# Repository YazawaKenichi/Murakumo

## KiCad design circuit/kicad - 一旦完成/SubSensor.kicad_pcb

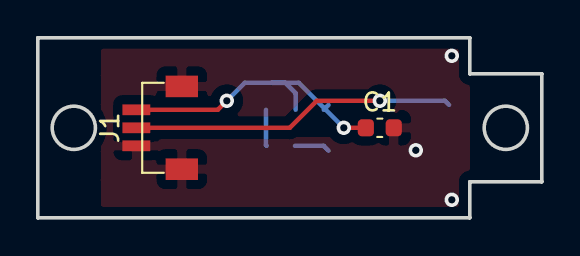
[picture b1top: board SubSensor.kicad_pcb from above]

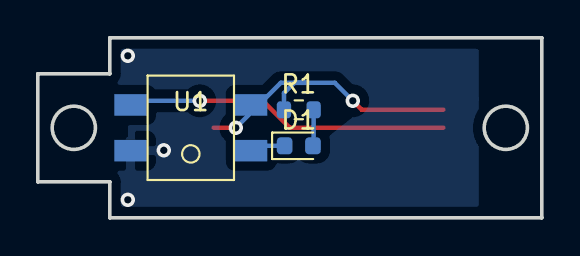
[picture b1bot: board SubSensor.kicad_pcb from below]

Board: 2 copper layers, 28.0 x 10.0 mm, 5 parts (3 on the bottom side), 5 nets.

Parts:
C1: 0.1u; C_0603_1608Metric
D1: SIR19-21C/TR8; D_0603_1608Metric
J1: SH3; SH_01x03
R1: 68; R_0603_1608Metric
U1: S7136

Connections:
+5V: C1.1, J1.3, R1.1, U1.2
GND: C1.2, J1.1, J1.MP, U1.4
unnamed: D1.1, U1.1
unnamed: D1.2, R1.2
unnamed: J1.2, U1.3

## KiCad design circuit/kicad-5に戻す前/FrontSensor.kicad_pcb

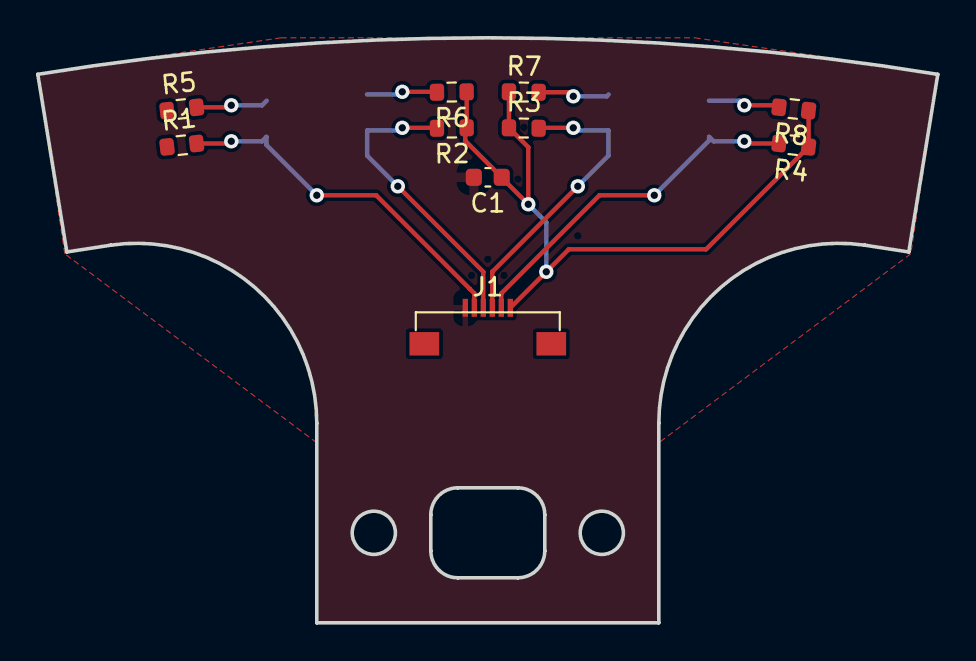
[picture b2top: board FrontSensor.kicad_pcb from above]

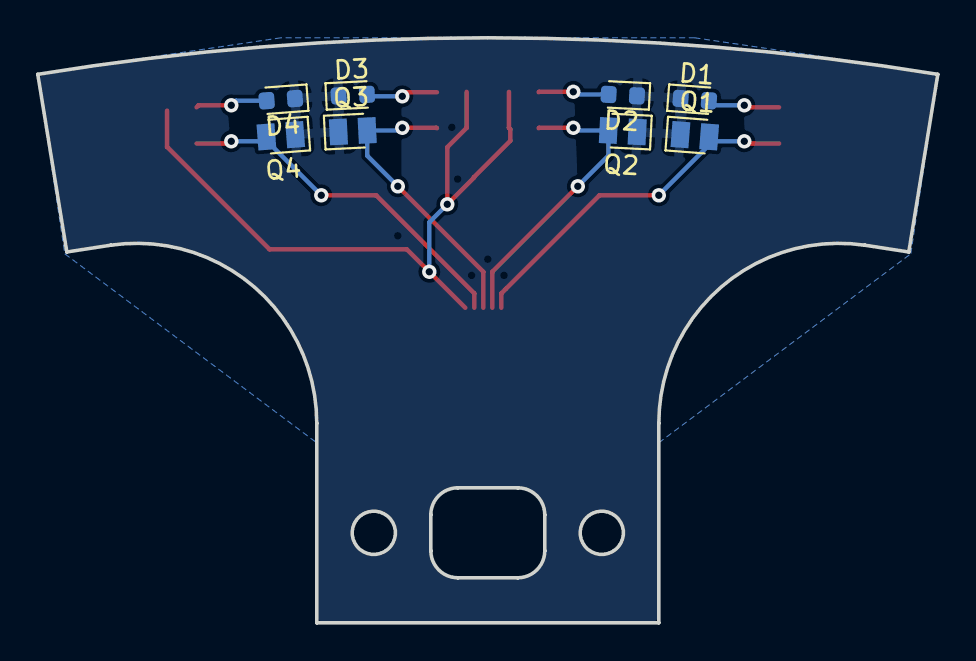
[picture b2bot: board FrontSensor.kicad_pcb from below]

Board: 2 copper layers, 50.0 x 32.5 mm, 18 parts (8 on the bottom side), 10 nets.

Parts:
C1: 0.1u; C_0603_1608Metric
D1, D2, D3, D4: SIR19-21C/TR8; D_0603_1608Metric
J1: FFC6; Molex_0545480671_01x06_P0.5mm
Q1, Q2, Q3, Q4: TEMT7100X01
R1, R2, R3, R4: 10k; R_0603_1608Metric
R5, R6, R7, R8: 100; R_0603_1608Metric

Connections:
+3V3: C1.1, J1.6, R1.1, R2.1, R3.1, R4.1, R5.1, R6.1, R7.1, R8.1
GND: C1.2, D1.1, D2.1, D3.1, D4.1, J1.1, Q1.2, Q2.2, Q3.2, Q4.2
unnamed: D1.2, R5.2
unnamed: D2.2, R6.2
unnamed: D3.2, R7.2
unnamed: D4.2, R8.2
unnamed: J1.2, Q1.1, R1.2
unnamed: J1.3, Q2.1, R2.2
unnamed: J1.4, Q3.1, R3.2
unnamed: J1.5, Q4.1, R4.2

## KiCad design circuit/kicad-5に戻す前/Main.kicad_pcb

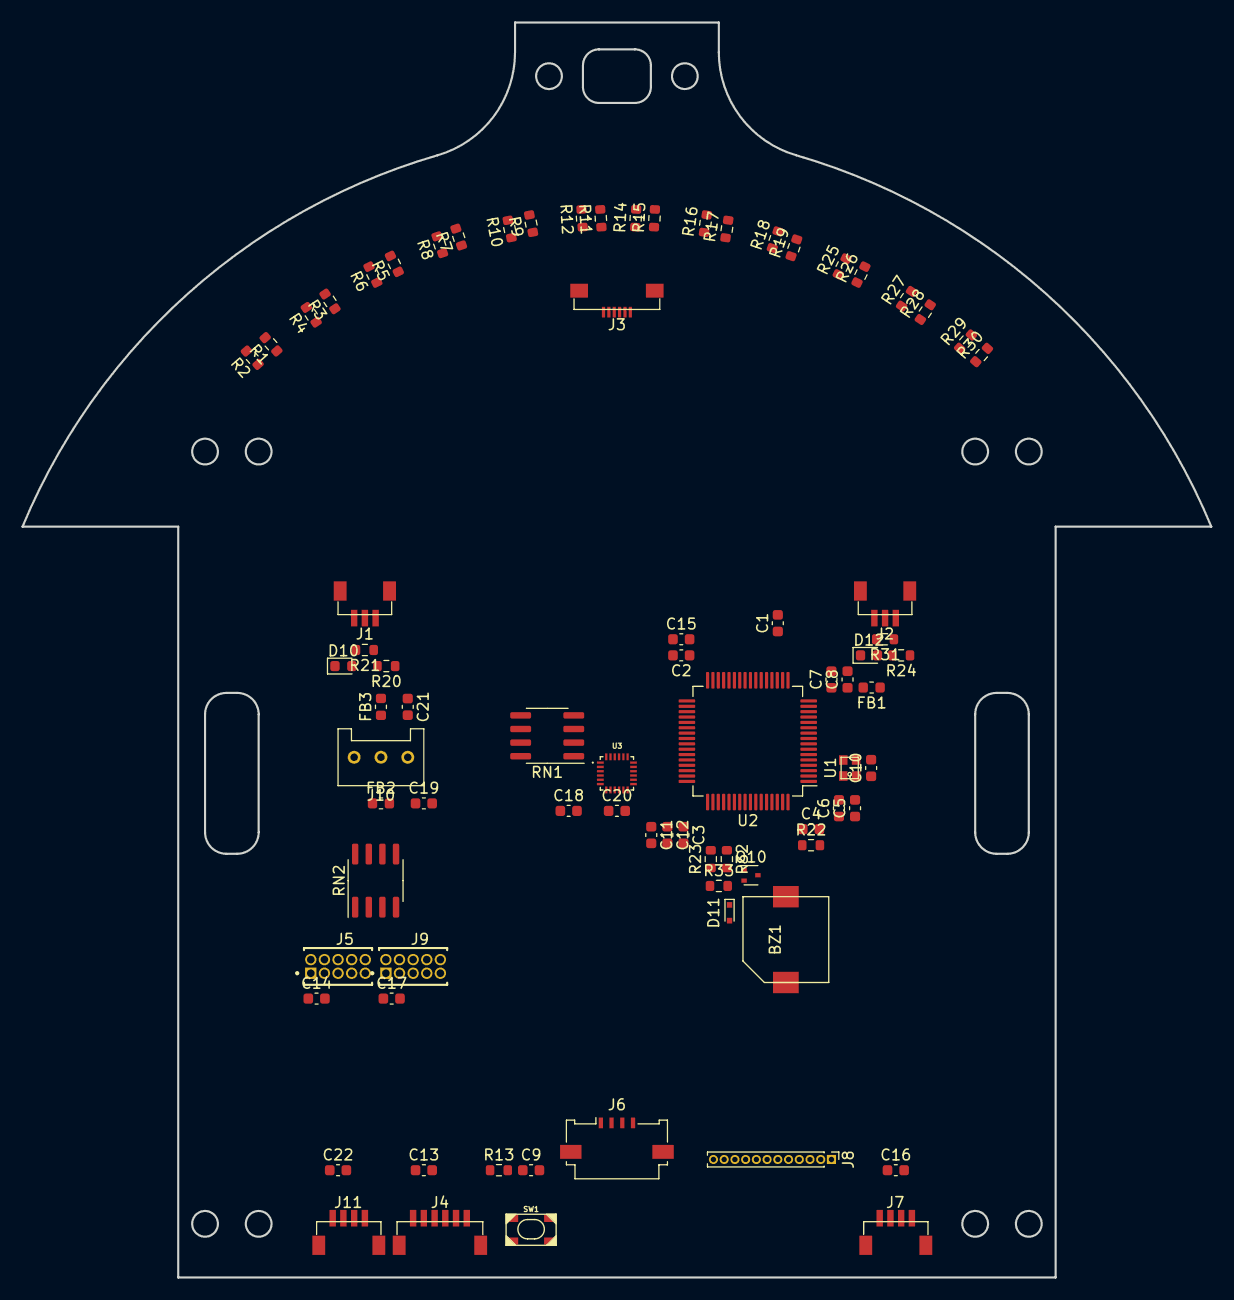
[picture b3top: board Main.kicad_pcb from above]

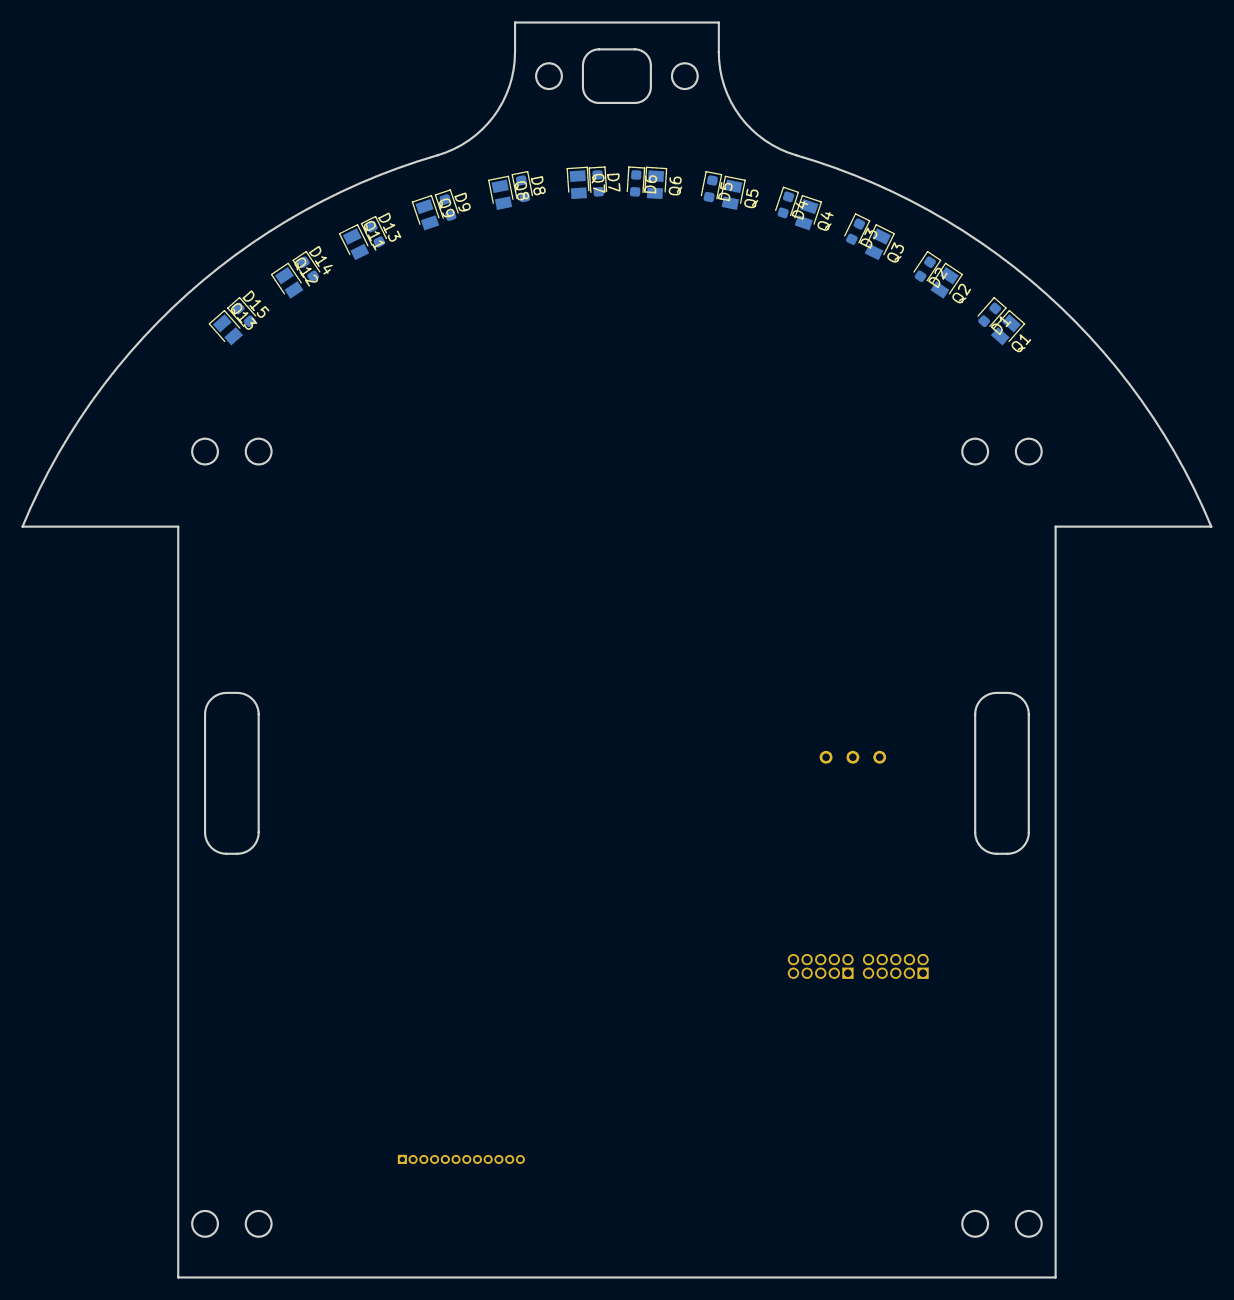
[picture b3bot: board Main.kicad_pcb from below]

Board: 2 copper layers, 110.8 x 117.0 mm, 104 parts (24 on the bottom side), 79 nets, no tracks yet.

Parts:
BZ1: TE044003-4
C1, C2, C3, C4, C6, C7, C9, C10, C13, C14, C15, C16, C17, C18, C19, C20, C21, C22: 0.1u; C_0603_1608Metric
C5: 4.7u; C_0603_1608Metric
C8: 1u; C_0603_1608Metric
C11, C12: 2.2u; C_0603_1608Metric
D1, D2, D3, D4, D5, D6, D7, D8, D9, D13, D14, D15: SIR19-21C/TR8; D_0603_1608Metric
D10, D12: SMLEN3WBC8W1; D_0603_1608Metric
D11: RB751S40-AU_R1_000A1; SOD-523
FB1, FB2, FB3: 470; L_0603_1608Metric
J1, J2: SH3; SH_01x03
J3: FFC6; Molex_0545480671_01x06_P0.5mm
J4: SH6; SH_01x06
J5, J9: FTSH2x5; SAMTEC_FTSH-105-01-L-D-K
J6: FFC4; Molex_200528-0040_1x04-1MP_P1.00mm_Horizontal
J7, J11: SH4; SH_01x04
J8: FFC12; PinHeader_1x12_P1.00mm_Vertical
J10: PA3; PA_01x03
Q1, Q2, Q3, Q4, Q5, Q6, Q7, Q8, Q9, Q11, Q12, Q13: TEMT7100X01
Q10: 2N7002T; SOT-523
R1, R3, R5, R7, R9, R11, R14, R16, R18, R23, R25, R27, R29: 100; R_0603_1608Metric
R2, R4, R6, R8, R10, R12, R13, R15, R17, R19, R21, R22, R26, R28, R30, R31, R32: 10k; R_0603_1608Metric
R20, R24: 470; R_0603_1608Metric
R33: 36; R_0603_1608Metric
RN1, RN2: 10k; SOIC-8_3.9x4.9mm_P1.27mm
SW1: SKRPABE010
U1: ASTMLPA-16MHz-LJ-E-T; ASTMLPA-16.000MHz-LJ-E-T
U2: STM32F405RGTx; LQFP-64_10x10mm_P0.5mm
U3: ICM-20648; QFN40P300X300X95-24N

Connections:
+3V3: BZ1.1, C1.1, C2.1, C3.1, C4.1, C5.1, C6.1, C10.1, C13.1, C15.1, C16.1, C18.1, C21.1, D11.1, FB1.1, FB3.2, J3.1, J4.1, J7.1, R1.1, R2.1, R3.1, R4.1, R5.1, R6.1, R7.1, R8.1, R9.1, R10.1, R11.1, R12.1, R13.1, R14.1, R15.1, R16.1, R17.1, R18.1, R19.1, R25.1, R26.1, R27.1, R28.1, R29.1, R30.1, RN1.5, RN1.6, RN1.7, RN1.8, U1.4, U2.1, U2.19, U2.32, U2.48, U2.64, U3.8, U3.13
+5V: C14.1, C17.1, C19.1, C22.1, FB2.2, J1.1, J2.1, J5.2, J9.2, J11.1, R20.1, R21.1, R24.1, R31.1, RN2.5, RN2.6, RN2.7, RN2.8
/DRV1_EN: J6.1, U2.54
/DRV1_PN: J6.2, U2.58
/DRV2_EN: J6.4, U2.2
/DRV2_PN: J6.3, U2.59
/LED_B: J8.3, U2.51
/LED_G: J8.4, U2.52
/LED_R: J8.5, U2.53
/LED_Red: J8.1, U2.39
/LED_White: J8.2, U2.40
/Rotary1: J8.9, U2.45
/Rotary2: J8.7, U2.44
/Rotary4: J8.6, U2.43
/Rotary8: J8.8, U2.34
/SW1: J8.10, U2.3
/SW2: J8.11, U2.4
/SW3: J8.12, U2.6
/Sensor01: Q1.1, R2.2, U2.27
/Sensor02: Q2.1, R4.2, U2.26
/Sensor03: Q3.1, R6.2, U2.25
/Sensor04: Q4.1, R8.2, U2.24
/Sensor05: Q5.1, R10.2, U2.23
/Sensor06: Q6.1, R12.2, U2.22
/Sensor07: Q7.1, R15.2, U2.21
/Sensor08: Q8.1, R17.2, U2.20
/Sensor09: Q9.1, R19.2, U2.17
/Sensor10: Q11.1, R26.2, U2.16
/Sensor11: Q12.1, R28.2, U2.15
/Sensor12: Q13.1, R30.2, U2.14
Encorder1_A: J5.6, RN2.1, U2.41
Encorder1_B: J5.8, RN2.2, U2.42
Encorder2_A: J9.6, RN2.3, U2.56
Encorder2_B: J9.8, RN2.4, U2.57
GND: C1.2, C2.2, C3.2, C4.2, C5.2, C6.2, C7.2, C8.2, C9.2, C10.2, C11.2, C12.2, C13.2, C14.2, C15.2, C16.2, C17.2, C18.2, C19.2, C20.2, C21.2, C22.2, D1.1, D2.1, D3.1, D4.1, D5.1, D6.1, D7.1, D8.1, D9.1, D13.1, D14.1, D15.1, J1.3, J2.3, J3.6, J4.3, J5.3, J7.4, J9.3, J10.3, J11.2, Q1.2, Q2.2, Q3.2, Q4.2, Q5.2, Q6.2, Q7.2, Q8.2, Q9.2, Q11.2, Q12.2, Q13.2, R22.2, R32.1, R33.1, SW1.2, U1.2, U2.12, U2.18, U2.63, U3.11, U3.18, U3.20
I2C_SCL: J7.2, U2.61
I2C_SDA: J7.3, U2.62
ICM_MISO: RN1.3, U2.35, U3.9
ICM_MOSI: RN1.2, U2.36, U3.24
ICM_SCLK: RN1.1, U2.29, U3.23
ICM_nCS: RN1.4, U2.33, U3.22
unnamed: BZ1.2, D11.2, Q10.3
unnamed: C7.1, C8.1, FB1.2, U2.13
unnamed: C11.1, U2.31
unnamed: C12.1, U2.47
unnamed: C20.1, U3.10
unnamed: D1.2, R1.2
unnamed: D2.2, R3.2
unnamed: D3.2, R5.2
unnamed: D4.2, R7.2
unnamed: D5.2, R9.2
unnamed: D6.2, R11.2
unnamed: D7.2, R14.2
unnamed: D8.2, R16.2
unnamed: D9.2, R18.2
unnamed: D10.2, R20.2
unnamed: D12.2, R24.2
unnamed: D13.2, R25.2
unnamed: D14.2, R27.2
unnamed: D15.2, R29.2
unnamed: FB2.1, J10.1
unnamed: FB3.1, J10.2
unnamed: J3.2, U2.8
unnamed: J3.3, U2.9
unnamed: J3.4, U2.10
unnamed: J3.5, U2.11
unnamed: Q10.1, R23.1, R32.2
unnamed: Q10.2, R33.2
unnamed: R22.1, U2.60
unnamed: R23.2, U2.50
unnamed: U1.3, U2.5
SWCLK: J4.2, U2.49
SWDIO: J4.4, U2.46
SWO: J4.6, U2.55
SubSens1: D12.1, J2.2, R31.2, U2.28
SubSens2: D10.1, J1.2, R21.2, U2.30
USART_RX: J11.4, U2.38
USART_TX: J11.3, U2.37
nRST: C9.1, J4.5, R13.2, SW1.1, U2.7

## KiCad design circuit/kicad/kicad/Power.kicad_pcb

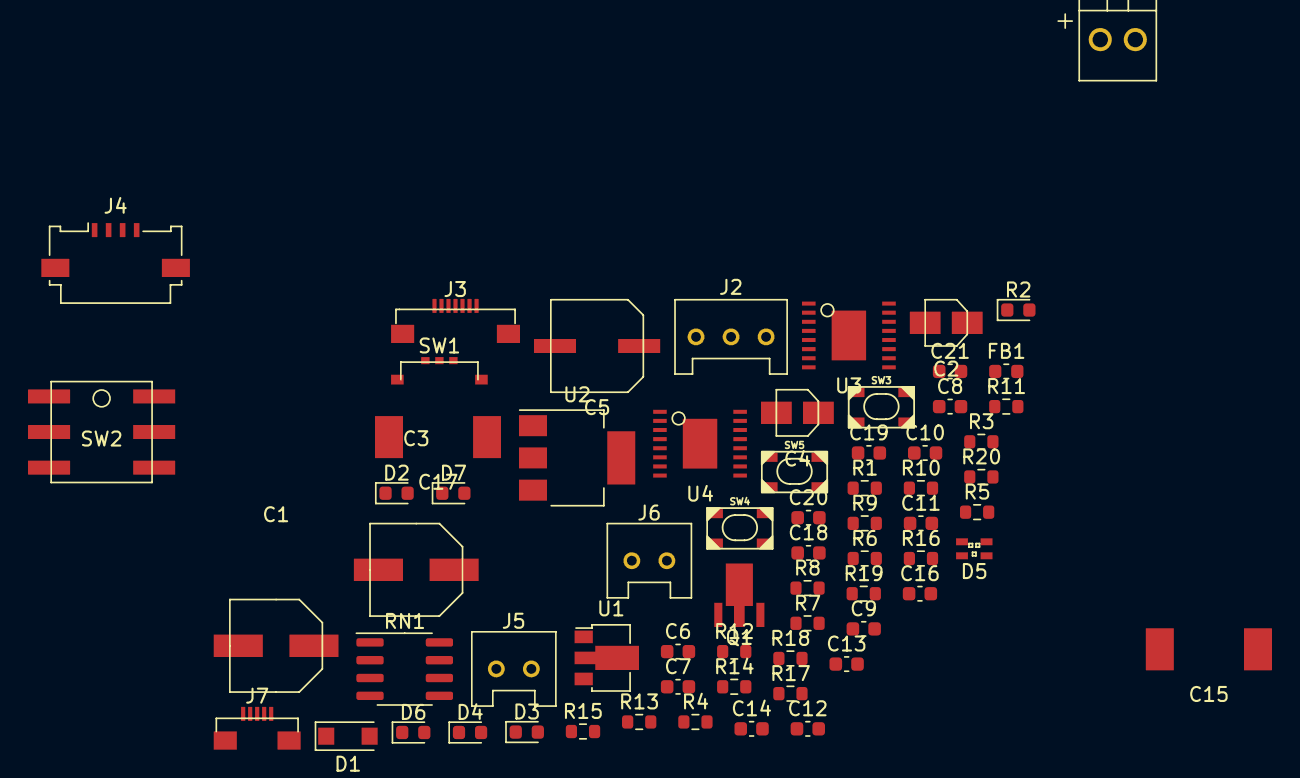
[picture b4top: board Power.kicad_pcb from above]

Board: 2 copper layers, 67 parts (0 on the bottom side), 48 nets, no tracks yet.

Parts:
C1, C3: 10u; AVE106M16A12T-F
C2, C4: 22u; 865090168010
C5: 220u; EEE-1AA221XP
C6, C7, C8, C9, C10, C11, C12, C13, C14, C16, C18, C19: 0.1u; C_0603_1608Metric
C15, C17: 100u; ECASD91B107M012K00
C20, C21: 22n; C_0603_1608Metric
D1: SS2040FL-AU_R1_000A1; SOD-123FL
D2: Red; D_0603_1608Metric
D3: Orange; D_0603_1608Metric
D4: Yellow; D_0603_1608Metric
D5: APTF1616LSEEZGKQBKC
D6, D7: SMLEN3WBC8W1; D_0603_1608Metric
FB1: 470; L_0603_1608Metric
J1: ILG2; ILG_01x02
J2: PA3; PA_01x03
J3: FFC7; Molex_0545480771_01x07_P0.5mm
J4: FFC4; Molex_200528-0040_1x04-1MP_P1.00mm_Horizontal
J5, J6: PA2; PA_01x02
J7: FFC5; Molex_0545480571_01x05_P0.5mm
Q1: CXDM4060P; SOT-89
R1, R5, R6, R7, R8, R9: 10k; R_0603_1608Metric
R2: 2k; D_0603_1608Metric
R3: 680; R_0603_1608Metric
R4: 270; R_0603_1608Metric
R10, R13: 16k; R_0603_1608Metric
R11, R12: 470; R_0603_1608Metric
R14, R20: 50k; R_0603_1608Metric
R15, R16, R18, R19: 1.2k; R_0603_1608Metric
R17: 1.5k; R_0603_1608Metric
RN1: 10k; SOIC-8_3.9x4.9mm_P1.27mm
SW1: SW_DPDT_x2; SSAJ120100
SW2: 220AMB16R
SW3, SW4, SW5: SKRPABE010
U1: AZ1117R-5.0TRE1; SOT-89-3
U2: AZ1117IH-3.3TRG1; SOT-223-3_TabPin2
U3, U4: DRV8874; TSSOP_16-Pin

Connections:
+3V3: C4.1, J2.2, R4.1, R5.1, R6.1, R7.1, R8.1, R9.1, R10.1, R13.1, RN1.5, RN1.6, RN1.7, RN1.8, U2.2
+5V: C2.1, C3.1, D5.1, J2.1, R3.1, R11.1, R12.1, U1.2, U2.3
+BATT: C5.1, C6.1, C14.1, C15.1, C16.1, C17.1, C18.1, C19.1, D1.2, Q1.2, R2.1, U3.11, U4.11
/DRV1_EN: J4.1, U3.1
/DRV1_PN: J4.2, U3.2
/DRV2_EN: J4.3, U4.1
/DRV2_PN: J4.4, U4.2
/Rotary1: C10.1, J3.1, RN1.4, SW2.1
/Rotary2: C9.1, J3.2, RN1.3, SW2.2
/Rotary4: C8.1, J3.3, RN1.2, SW2.4
/Rotary8: C7.1, J3.4, RN1.1, SW2.8
/SW1: C13.1, J3.5, R7.2, SW5.1
/SW2: C12.1, J3.6, R6.2, SW4.1
/SW3: C11.1, J3.7, R5.2, SW3.1
GND: C1.2, C2.2, C3.2, C4.2, C5.2, C6.2, C7.2, C8.2, C9.2, C10.2, C11.2, C12.2, C13.2, C14.2, C15.2, C16.2, C17.2, D2.1, D3.1, D4.1, J2.3, R14.2, R15.2, R16.2, R20.2, SW1.2, SW2.C, SW3.2, SW4.2, SW5.2, U1.1, U2.1, U3.7, U3.9, U3.15, U3.16, U4.7, U4.9, U4.15, U4.16
unnamed: C1.1, FB1.1, U1.3
unnamed: C18.2, U3.12
unnamed: C19.2, U4.12
unnamed: C20.1, U3.13
unnamed: C20.2, U3.14
unnamed: C21.1, U4.13
unnamed: C21.2, U4.14
unnamed: D1.1, FB1.2
unnamed: D2.2, R2.2
unnamed: D3.2, R3.2
unnamed: D4.2, R4.2
unnamed: D5.2, R19.1
unnamed: D5.3, R18.1
unnamed: D5.4, R17.1
unnamed: D6.1, J7.2
unnamed: D6.2, R11.2
unnamed: D7.1, J7.1
unnamed: D7.2, R12.2
unnamed: J1.2, Q1.3, R1.1
unnamed: J5.1, U3.10
unnamed: J5.2, U3.8
unnamed: J6.1, U4.10
unnamed: J6.2, U4.8
unnamed: J7.3, R19.2
unnamed: J7.4, R18.2
unnamed: J7.5, R17.2
unnamed: Q1.1, R1.2, SW1.3
unnamed: R8.2, U3.3, U3.4
unnamed: R9.2, U4.3, U4.4
unnamed: R10.2, R14.1, U4.5
unnamed: R13.2, R20.1, U3.5
unnamed: R15.1, U3.6
unnamed: R16.1, U4.6
